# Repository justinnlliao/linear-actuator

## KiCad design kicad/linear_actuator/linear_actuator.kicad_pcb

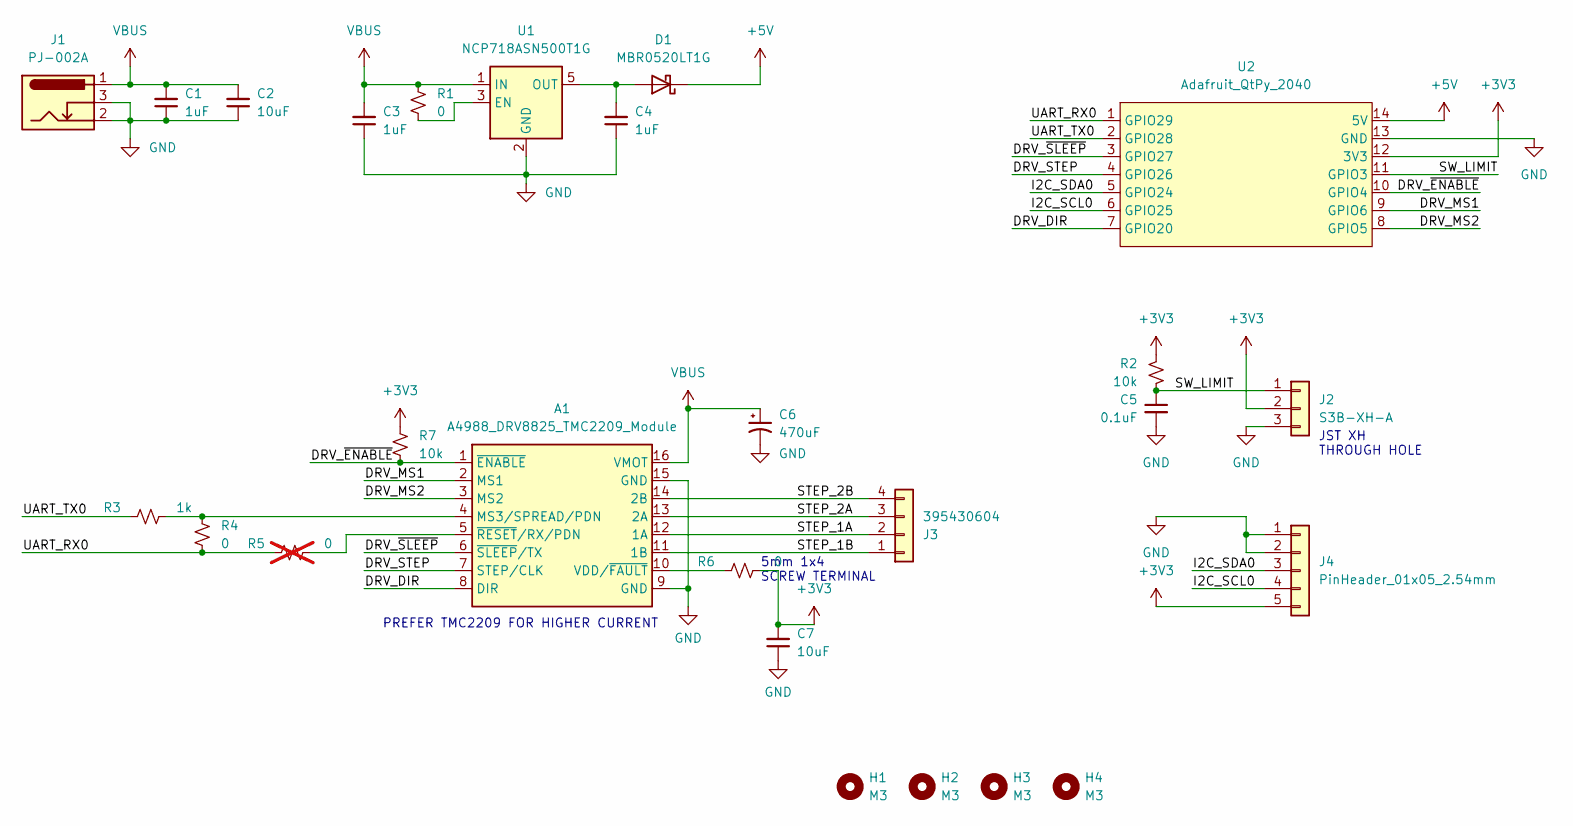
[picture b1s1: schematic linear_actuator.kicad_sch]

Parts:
A1: A4988_DRV8825_TMC2209_Module; Pololu_Breakout-16_15.2x20.3mm; Digikey AMAZON
C1, C3, C4: 1uF; C_0603_1608Metric_Pad1.08x0.95mm_HandSolder; Digikey IN HOUSE
C2, C7: 10uF; C_0603_1608Metric_Pad1.08x0.95mm_HandSolder; Digikey IN HOUSE
C5: 0.1uF; C_0603_1608Metric_Pad1.08x0.95mm_HandSolder; Digikey IN HOUSE
C6: 470uF; CP_Radial_D8.0mm_P2.50mm
D1: MBR0520LT1G; D_SOD-123
H1, H2, H3, H4: M3; MountingHole_3.2mm_M3; Digikey NA
J1: PJ-002A; BarrelJack_Horizontal
J2: S3B-XH-A; JST_XH_S3B-XH-A_1x03_P2.50mm_Horizontal
J3: 395430604; TerminalBlock_Molex_395430604_1x04_P5.00mm_Horizontal; Digikey SAMPLE
J4: PinHeader_01x05_2.54mm; PinHeader_1x05_P2.54mm_Vertical; Digikey IN HOUSE
R1, R4, R6: 0; R_0603_1608Metric_Pad0.98x0.95mm_HandSolder; Digikey IN HOUSE
R2, R7: 10k; R_0603_1608Metric_Pad0.98x0.95mm_HandSolder; Digikey IN HOUSE
R3: 1k; R_0603_1608Metric_Pad0.98x0.95mm_HandSolder; Digikey IN HOUSE
R5: 0; R_0603_1608Metric_Pad0.98x0.95mm_HandSolder; Digikey IN HOUSE; not fitted
U1: NCP718ASN500T1G; SOT-23-5_HandSoldering
U2: Adafruit_QtPy_2040; MOUDLE14P-2.54-21X17.8MM

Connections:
+3V3: C7.2, J2.2, J4.5, R2.1, R6.2, R7.1, U2.12 (3V3)
+5V: D1.1 (K), U2.14 (5V)
/DRV_DIR: A1.8 (DIR), U2.7 (GPIO20)
/DRV_MS1: A1.2 (MS1), U2.9 (GPIO6)
/DRV_MS2: A1.3 (MS2), U2.8 (GPIO5)
/DRV_STEP: A1.7 (STEP/CLK), U2.4 (GPIO26)
/DRV_~ENABLE: A1.1 (~ENABLE), R7.2, U2.10 (GPIO4)
/DRV_~SLEEP: A1.6 (~SLEEP/TX), U2.3 (GPIO27)
/I2C_SCL0: J4.4, U2.6 (GPIO25)
/I2C_SDA0: J4.3, U2.5 (GPIO24)
/STEP_1A: A1.12 (1A), J3.2
/STEP_1B: A1.11 (1B), J3.1
/STEP_2A: A1.13 (2A), J3.3
/STEP_2B: A1.14 (2B), J3.4
/SW_LIMIT: C5.1, J2.1, R2.2, U2.11 (GPIO3)
/UART_RX0: R4.2, R5.1, U2.1 (GPIO29)
/UART_TX0: R3.1, U2.2 (GPIO28)
GND: A1.9 (GND), A1.15 (GND), C1.1, C2.1, C3.1, C4.1, C5.2, C6.2, C7.1, J1.2, J1.3, J2.3, J4.1, J4.2, U1.2 (GND), U2.13 (GND)
unnamed: A1.4 (MS3/SPREAD/PDN), R3.2, R4.1
unnamed: A1.10 (VDD/~FAULT), R6.1
unnamed: A1.5 (~RESET/RX/PDN), R5.2
unnamed: C4.2, D1.2 (A), U1.5 (OUT)
unnamed: R1.2, U1.3 (EN)
VBUS: A1.16 (VMOT), C1.2, C2.2, C3.2, C6.1, J1.1, R1.1, U1.1 (IN)

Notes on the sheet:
5mm 1x4 SCREW TERMINAL
PREFER TMC2209 FOR HIGHER CURRENT
JST XH THROUGH HOLE

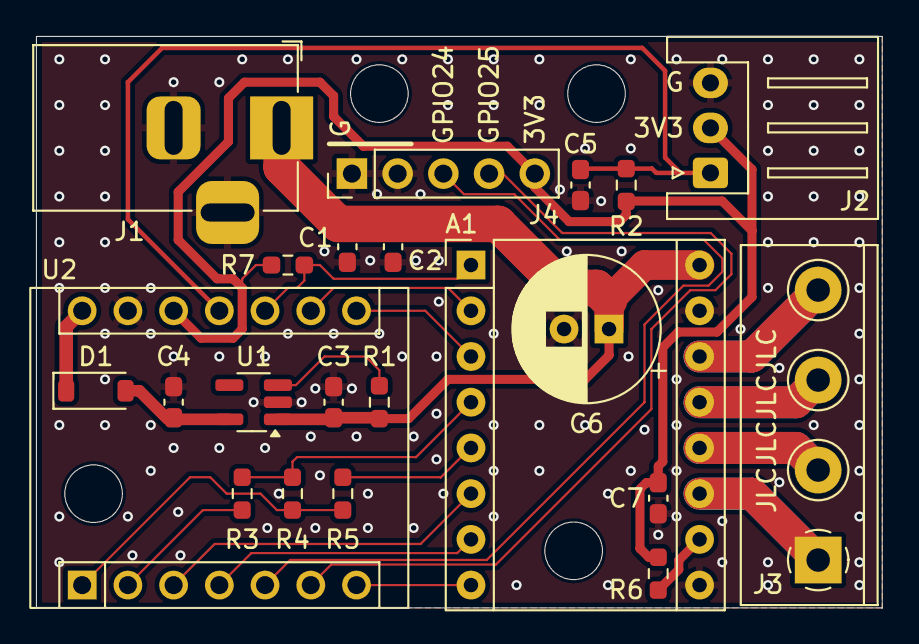
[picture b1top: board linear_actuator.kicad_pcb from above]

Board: 2 copper layers, 47.0 x 31.8 mm, 26 parts (0 on the bottom side), 24 nets.

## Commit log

2024-07-03 first iteration
    created all files and put 2 main chips
2024-07-03 Add 3d model to footprint
2024-07-03 more work
2024-07-03 git ignore add
2024-07-03 power stuff done
2024-07-03 schem done
2024-07-03 just moved something lol
2024-07-03 more work (should have all footprints)
2024-07-04 Tidy up schematic and add limit switch connector
2024-07-07 Start reworking PCB
2024-07-07 Continue layout
2024-07-07 Pass DRC
2024-07-07 Add PU to keep driver enable off by default, and decorate
2024-07-07 Rearrange jumpers on UART lines
2024-07-08 Generate Gerbers
2024-07-08 able to change UART pins
2024-07-08 UART ports print properly
2024-07-08 initial positioning code
2024-07-10 more or less good for initial function
2024-07-10 reads commands from serial with some functions included
2024-07-10 UART port confirmed
2024-07-19 code changes
2024-07-19 mucho code done
2024-07-20 mucho more code
    ALL FUNCTIONING EXCEPT FOR THE STOP COMMAND CANT FIGURE OUT WHY
2024-07-24 code more or less finalized
2024-07-24 color coded movement but the Serial.available for software hardstop isn't working
    for(step blah blah) {
    step commands blah blah
    if(lengthCheck() == true || safetyStop() == true) {
    Serial.println("emergency stopped successfully");
    pixels.fill(0xFF0000);
    pixels.show();
2024-07-24 THE STOP WORKS (also less green)
2026-04-24 Remove description
